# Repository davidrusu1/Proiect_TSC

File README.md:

# InkTime — Smartwatch Open Source

Un smartwatch proiectat de la zero — schematic, PCB 4 straturi, model 3D complet — bazat pe nRF52840 și un display E-Paper cu consum zero în standby.

---

## Despre proiect

InkTime este un ceas inteligent construit integral custom: fiecare componentă a fost aleasă, plasată și rutată manual, de la primul simbol în schematic până la modelul 3D pregătit pentru fabricație.

Tehnologia centrală este display-ul **E-Paper (e-ink)** — după ce afișează o imagine, o menține fără niciun consum de energie. Combinat cu modul deep sleep al nRF52840 (~1.5μA), dispozitivul poate funcționa zile întregi dintr-o baterie LiPo mică.

---

## Ce conține placa

| Subsistem | Componentă | Rol |
|---|---|---|
| Microcontroller | nRF52840 | Cortex-M4 64MHz, BT 5.0, USB nativ |
| Display | E-Paper via SPI | Afișaj fără consum în standby |
| Mișcare | BMA423 | Accelerometru 3 axe, step counter, wake-on-wrist |
| Încărcare | BQ25180 | LiPo charger programabil I2C, 5mA–1A |
| Alimentare | RT6160 | Buck-Boost 3.3V stabil indiferent de tensiunea bateriei |
| Fuel Gauge | MAX17048 | Monitorizare baterie ModelGauge, fără shunt rezistor |
| Feedback haptic | DRV2605 | Driver haptic I2C, 123 efecte ERM/LRA |
| USB | KH-TYPE-C-16P + USBLC6 | Conector USB-C cu protecție ESD ±15kV |
| Butoane | EVP-AKE31A ×3 | Butoane tactile SMD ultra-subțiri |
| RF | 2450AT18B100E | Antenă SMD 2.45GHz pentru Bluetooth |

---

## Diagrama bloc a sistemului

```
USB-C (5V)
    │
    ▼
┌─────────┐    VBUS      ┌──────────────┐
│  ESD    │─────────────▶│  BQ25180     │ LiPo Charger
│USBLC6   │              │  (I2C 0x6A)  │◀─── Baterie LiPo
└────┬────┘              └──────┬───────┘
     │ D+/D−                    │ VBAT
     │                          ▼
     │                   ┌──────────────┐
     │                   │  MAX17048    │ Fuel Gauge
     │                   │  (I2C 0x36)  │
     │                   └──────┬───────┘
     │                          │ VBAT
     │                          ▼
     │                   ┌──────────────┐
     │                   │   RT6160     │ Buck-Boost DC/DC
     │                   │  (I2C 0x62)  │─── 3V3 ──────────┐
     │                   └──────────────┘                   │
     │                                                      │
     └──────────────────────────────────────────────────────▼
                                                    ┌──────────────────┐
                  ┌── SPI ──▶ E-Paper Display       │                  │
                  │                                  │    nRF52840      │
                  ├── I2C ──▶ BMA423  (0x18)        │    Cortex-M4     │
                  │       ──▶ DRV2605 (0x5A)        │    64MHz / BT5.0 │
                  │       ──▶ BQ25180 (0x6A)        │                  │
                  │       ──▶ RT6160  (0x62)        └────────┬─────────┘
                  │       ──▶ MAX17048(0x36)                 │
                  │                                          │ GPIO
                  ├── SWD ──▶ TC2030-IDC                     │
                  │                                          ▼
                  └── USB ──▶ (intern nRF52840)      Butoane ×3 / IMU INT / HAPTIC_EN
```

---

## BOM — Bill of Materials

| Ref | Part Number | Descriere | Qty |
|---|---|---|---|
| U1 | nRF52840-QIAA-R | MCU ARM Cortex-M4, BT 5.0, USB 2.0, 1MB Flash | 1 |
| IC1 | BQ25180YBGR | LiPo charger liniar 1A I2C, 8-DSBGA | 1 |
| IC2 | DRV2605YZFR | Haptic driver ERM/LRA I2C 123 efecte, 9-BGA | 1 |
| IC3 | BMA423 | Accelerometru MEMS triaxial 12-bit, LGA-12 | 1 |
| U3 | MAX17048G+T10 | Fuel gauge ModelGauge 1-cell, SOT-23-6 | 1 |
| IC9 | RT6160AWSC | Buck-Boost DC/DC 800mA I2C, 15-WL-CSP | 1 |
| D3 | USBLC6-2SC6Y | TVS ESD ±15kV bidirecțional USB, SOT-23-6 | 1 |
| J4 | KH-TYPE-C-16P | Conector USB-C 16 pini SMD | 1 |
| J1 | 503480-2400 | Conector FPC/FFC 0.5mm pas 24 circuite | 1 |
| J2 | TC2030-IDC | Tag-Connect SWD 6 pini footprint-only | 1 |
| Q2 | DMG2305UX-7 | P-MOSFET 20V/4.2A, SOT-23 | 1 |
| Q3 | SI1308EDL-T1-GE3 | N-MOSFET 30V/1.5A, SC-70 | 1 |
| D1,D2,D5 | MBR0530 | Schottky 30V/500mA, SOD-123 | 3 |
| SW_* | EVP-AKE31A | Buton tactil SMD ultra-subțire Panasonic | 3 |
| ANT1 | 2450AT18B100E | Antenă SMD 2.45GHz Johanson | 1 |
| L7 | FTC252012SR47MBCA | Inductor 0.47μH SMD 2016 | 1 |
| L5 | 744043680 | Inductor 68μH WE-TPC SMD | 1 |
| X1 | SXT21410EC27-32.000M | Cristal SMD 32MHz | 1 |
| X2 | NX3215SA-32.768K | Cristal RTC 32.768kHz 3215 SMD | 1 |
| Cx | GJM0335C1ER33WB01D / GRM011R60J152KE01L | Condensatoare SMD 0201/0402, 1pF–22μF | ~50 |
| Rx | ERA-1AEB / CPF0201 | Rezistoare SMD 0201, 2.2Ω–10kΩ | ~15 |
| TP_* | — | Test pad SMD | 14 |

---

## Hardware în detaliu

### Cum circulă energia

Bateria LiPo (3.7–4.2V) furnizează tensiunea de intrare pentru regulatorul **RT6160**, care generează un rail stabil de 3.3V pentru întreaga placă. La conectarea USB-C, VBUS (5V) ajunge direct la **BQ25180**, care preia controlul încărcării bateriei independent de restul sistemului. nRF52840 monitorizează în permanență cele două stări: prezența USB prin semnalul CHARGER_PG și nivelul bateriei prin **MAX17048** pe magistrala I2C.

Componentele cu consum ridicat — display-ul E-Paper și driverul haptic — sunt controlate fiecare printr-un MOSFET (Q2/Q3), permițând nRF52840 să le întrerupă complet alimentarea când nu sunt necesare.

---

### Magistrala I2C — 5 periferice pe aceleași fire

| Componentă | Adresă I2C | Funcție |
|---|---|---|
| BQ25180 | 0x6A | Reglează curentul și tensiunea de încărcare |
| RT6160 | 0x62 | Ajustează tensiunea de ieșire la nevoie |
| BMA423 | 0x18 | Furnizează date accelerometru și numără pași |
| MAX17048 | 0x36 | Raportează procentul de baterie și tensiunea celulei |
| DRV2605 | 0x5A | Selectează și redă efecte tactile |

Clock pe **P0.06**, date pe **P0.07**. Rezistoare de pull-up pe ambele linii.

---

### SPI — Display E-Paper

Comunicație unidirecțională spre display — nu există linie MISO deoarece displayul nu transmite date înapoi. Frecvență maximă 4MHz. Pe lângă SCK și MOSI, display-ul necesită 3 semnale GPIO suplimentare: **DC** (Data/Command), **RST** (reset hardware) și **BUSY** (MCU-ul așteaptă când displayul procesează un refresh).

---

### SWD — Programare și debug

Conectorul **TC2030-IDC** (Tag-Connect, fără pini fizici pe PCB) expune SWDIO, SWDCLK, SWO și RESET. Nu ocupă înălțime în ansamblu — cablul de programare se atașează temporar prin spring pins pe pad-urile PCB-ului.

---

### Bluetooth și antenă

Antena **2450AT18B100E** este o antenă SMD ceramică pentru 2.4GHz, plasată spre exteriorul plăcii cu un decupaj în substrat sub ea. Decupajul elimină FR4-ul (material cu pierderi dielectrice la 2.4GHz) din zona de radiație, îmbunătățind câștigul și adaptarea de impedanță a antenei. Cristalul de 32MHz furnizează referința de frecvență pentru modulul radio.

---

### Cristalul de 32.768kHz — RTC în sleep

Al doilea oscilator alimentează timer-ul RTC al nRF52840 și rămâne activ inclusiv în deep sleep. Permite dispozitivului să mențină ora exactă și să se trezească la intervale precise fără a ține procesorul activ.

---

### BMA423 — Mai mult decât un accelerometru

BMA423 dispune de un procesor intern dedicat pentru algoritmii de step counting și wake-on-wrist, care rulează independent de nRF52840. La detectarea mișcării specifice ridicării mâinii, trimite o întrerupere pe **P1.08 (IMU_INT1)** care trezește MCU-ul din deep sleep în microsecunde. Consum în această stare: 0.9μA.

---

### Estimare consum și autonomie

| Scenariu | Curent estimat |
|---|---|
| nRF52840 TX Bluetooth activ | 6.26 mA |
| nRF52840 RX Bluetooth activ | 4.82 mA |
| Refresh display E-Paper | ~26 mA (câteva secunde) |
| BMA423 monitorizare continuă | 130 μA |
| MAX17048 fuel gauge activ | 23 μA |
| DRV2605 vibrație activă | 5 mA |
| nRF52840 deep sleep + RTC + BMA low-power | ~50–100 μA |

Consum mediu în utilizare normală (BT conectat periodic, refresh display la fiecare minut, IMU activ): **6–8 mA la 3.3V**.

Cu o baterie LiPo de **300mAh**: autonomie estimată **35–50 ore**.

---

## Alocarea pinilor nRF52840

### Display E-Paper (SPI)

| Pin MCU | Semnal | Direcție | Descriere |
|---|---|---|---|
| P0.02 / AIN0 | SCK | OUT | Clock SPI pentru display |
| P0.03 / AIN1 | MOSI | OUT | Date seriale spre display |
| P0.05 / AIN3 | EPD_CS | OUT | Chip select, activ LOW |
| P0.15 | EPD_RST | OUT | Reset hardware display, activ LOW |
| P0.16 | EPD_DC | OUT | LOW = comandă, HIGH = date |
| P0.17 | EPD_BUSY | IN | HIGH când displayul procesează |

### Periferice I2C

| Pin MCU | Semnal | Descriere |
|---|---|---|
| P0.06 | SCL | Clock comun pentru toate perifericele I2C |
| P0.07 | SDA | Date bidirecționale I2C |
| P0.08 | IMU_INT2 | Întrerupere secundară BMA423 (step counter) |
| P1.08 | IMU_INT1 | Întrerupere primară BMA423 (wake-on-wrist) |
| P0.10 / NFC2 | FUELGAUGE_ALT | Alarmă MAX17048 la baterie scăzută |
| P0.11 | CHARGER_PG | Power Good BQ25180 — HIGH când USB e valid |
| P0.12 | HAPTIC_EN | Enable DRV2605, activ HIGH |

### Butoane

| Pin MCU | Semnal | Descriere |
|---|---|---|
| P0.13 | BTN_UP | Buton sus (navigare meniu) |
| P0.14 | BTN_ENT | Buton enter / confirmare |
| P1.02 | BTN_DN | Buton jos (navigare meniu) |

### USB, SWD și ceasuri

| Pin MCU | Semnal | Interfață | Descriere |
|---|---|---|---|
| D+ | USB_DP | USB | Linie diferențială pozitivă, prin ESD |
| D− | USB_DM | USB | Linie diferențială negativă, prin ESD |
| VBUS | 5V_USB | PWR | Detecție USB prezent → BQ25180 |
| SWDIO | SWDIO | SWD | Date programare/debug |
| SWDCLK | SWDCLK | SWD | Clock programare/debug |
| SWO | SWO | SWD | Serial Wire Output (trace) |
| P0.18 / RESET | RESET | GPIO | Reset hardware MCU |
| ANT | RF | RF | Antenă Bluetooth 2.4GHz |
| XC1, XC2 | XTAL_32M | CLK | Cristal 32MHz — clock principal |
| XL1, XL2 | XTAL_32K | CLK | Cristal 32.768kHz — RTC sleep |

---

## PCB — Decizii de proiectare

### 4 straturi

| Strat | Conținut |
|---|---|
| L1 — Top | Toate componentele SMD + rutare semnale principale |
| L2 | Plan de masă GND continuu |
| L3 | Plan de alimentare 3V3 |
| L4 — Bottom | Rutare secundară + conexiuni via |

Planul de masă pe L2 direct sub stratul de semnal L1 minimizează inductanța buclei de return. Planul de 3V3 pe L3 reduce impedanța de alimentare, esențial pentru vârfurile de curent ale nRF52840 în modul TX.

### Decupaj sub antenă

FR4-ul este un material cu pierderi dielectrice la 2.4GHz. Un decupaj fizic al PCB-ului sub jumătatea neconectată a antenei 2450AT18B100E permite acesteia să radieze în aer, îmbunătățind performanța RF.

### Test pad-uri

14 test pad-uri distribuite pe semnalele: 3V3, VBAT, GND, SDA, SCL, SWDCLK, SWDIO, SWO, RESET, VREG. Permit conectarea unui multimetru sau logic analyzer după asamblare.

### Erori acceptate

- **Board Outline Clearance** — erorile generate de markerii de dimensiuni și textele de silkscreen aflate lângă marginea plăcii au fost aprobate, deoarece nu afectează fabricabilitatea PCB-ului.
- **Copper Width** pe traseele de sub componentele BGA — lățimea a fost redusă local pentru a permite rutarea prin pitch-ul mic al pad-urilor BGA, apoi adusă înapoi la 0.3mm după ieșirea din zona BGA.

---

## Ansamblu 3D

Modelat complet în Autodesk Fusion 360. Stratificarea de jos în sus:

```
┌─────────────────────────┐  ← Cadru superior + geam display
│     Display E-Paper     │  ← Panou e-ink + cablu FPC
│         PCB             │  ← Placa cu toate componentele
│      Baterie LiPo       │  ← Celulă lipită direct pe test pad-uri
└─────────────────────────┘  ← Carcasă inferioară
```

Butoanele (×3) sunt accesibile prin locașurile laterale ale carcasei. Conectorul USB-C iese prin fanta frontală. Shaker-ul haptic este montat în spațiul rămas lângă baterie.

---

## Galerie

---

## Structura repository-ului

```
InkTime/
│
├── Hardware/
│   ├── PCB.brd                  # Fișier board Fusion Electronics
│   ├── Schematic_Final.sch      # Schematic complet
│   └── Schematic_Final.pdf      # Export PDF schematic
│
├── Manufacturing/
│   ├── gerbers.zip              # Fișiere Gerber pentru fabricație
│   ├── InkTime.bom              # Bill of Materials
│   └── PnP_InkTime_front.cpl   # Pick & Place față
│
├── Mechanical/
│   ├── Exploded_Watch3D.zip    # Exported STEP ansamblu exploded view
│   └── Assembled Watch.f3z           # Proiect Autodesk Fusion 360
│
├── Images/                      # Randări și capturi PCB
│
├── LICENSE
└── README.md
```

---

MIT License — Copyright 2026 Rusu David Gabriel

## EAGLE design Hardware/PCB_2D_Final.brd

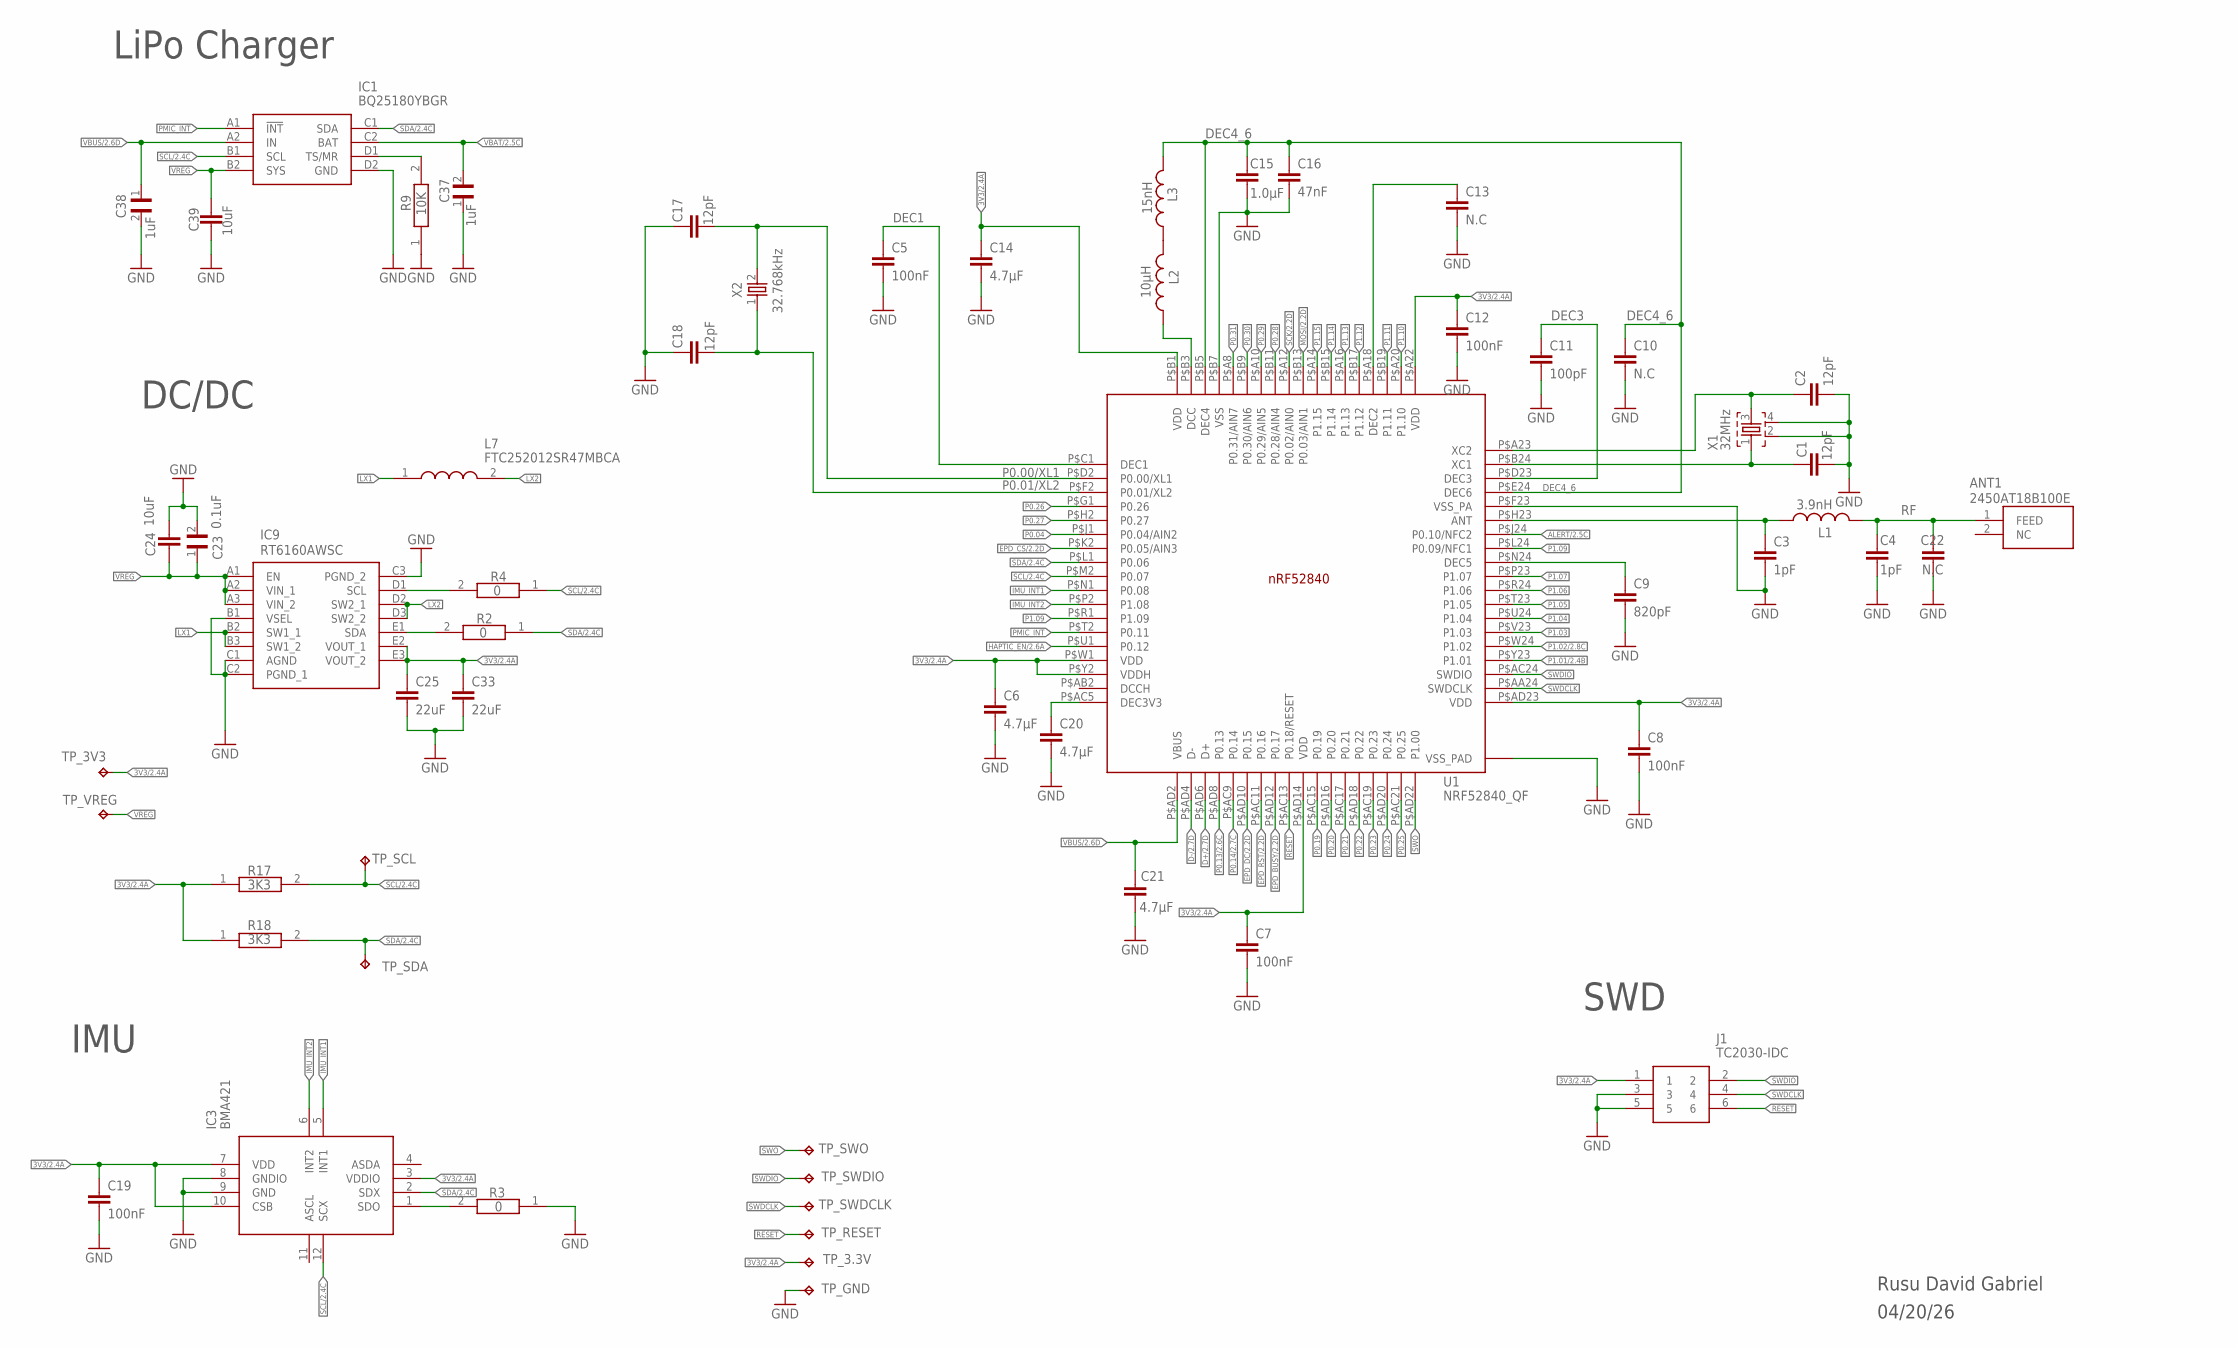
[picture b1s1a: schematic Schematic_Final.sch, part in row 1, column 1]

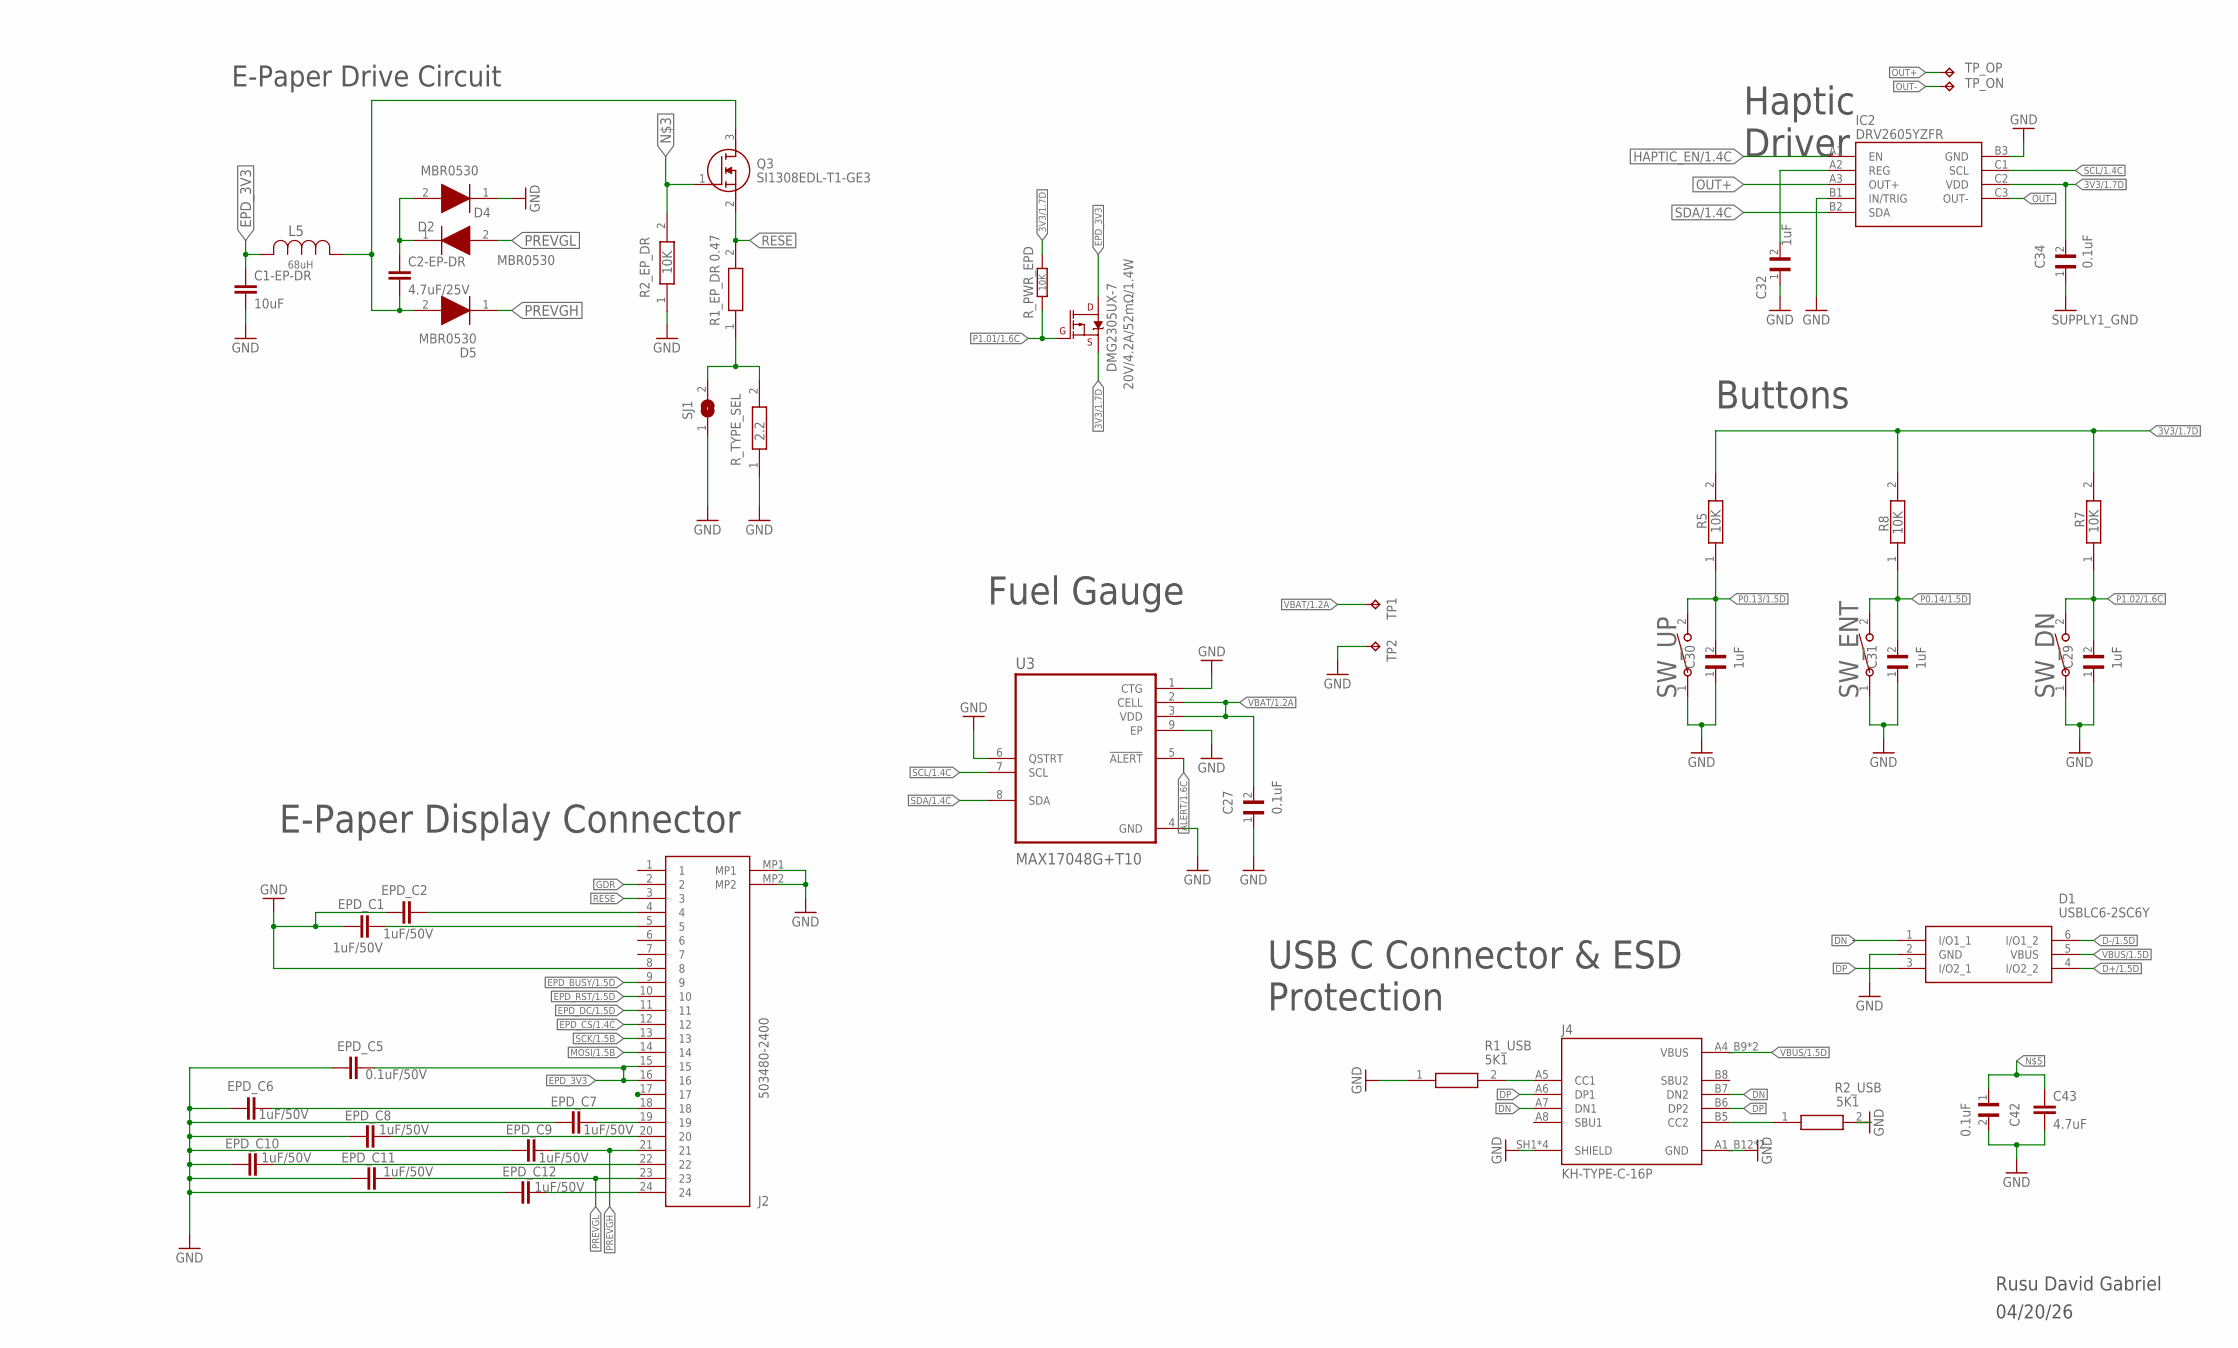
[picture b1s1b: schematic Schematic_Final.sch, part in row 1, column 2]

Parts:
ANT1: 2450AT18B100E; 2450AT18B100E_ANTC3216X140N
C1, C2, C17, C18: 12pF; NORDIC_NRF_3_RESC0201_L
C1-EP-DR, C24, C39: 10uF; NORDIC_NRF_3_RESC0402_L
C2-EP-DR: 4.7uF/25V; NORDIC_NRF_3_RESC0402_L
C3, C4: 1pF; NORDIC_NRF_3_RESC0201_L
C5, C7, C8, C12, C19: 100nF; NORDIC_NRF_3_RESC0201_L
C6, C14, C20, C21: 4.7μF; NORDIC_NRF_3_RESC0402_L
C9: 820pF; NORDIC_NRF_3_RESC0201_L
C10, C13, C22: N.C; NORDIC_NRF_3_RESC0201_L
C11: 100pF; NORDIC_NRF_3_RESC0201_L
C15: 1.0μF; NORDIC_NRF_3_RESC0402_L
C16: 47nF; NORDIC_NRF_3_RESC0201_L
C23, C27, C34, C42: 0.1uF; GRM011R60J152KE01L_2_CAPC0201X13N
C25, C33: 22uF; NORDIC_NRF_3_RESC0402_L
C29, C30, C31, C32, C37, C38: 1uF; GRM011R60J152KE01L_2_CAPC0201X13N
C43: 4.7uF; NORDIC_NRF_3_RESC0402_L
D1: USBLC6-2SC6Y; ESP32_C6_LIBRARY_3_SOT95P280X145-6N
D2, D4, D5: MBR0530; ESP32_C6_LIBRARY_5_SOD3716X135N
DMG2305UX-7: 20V/4.2A/52mΩ/1.4W; ESP32_C6_LIBRARY_4_ESP32_C6_LIBRARY_4_ESP32_C6_LIBRARY_4_ES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
EPD_C1, EPD_C2, EPD_C6, EPD_C7, EPD_C8, EPD_C9, EPD_C10, EPD_C11, EPD_C12: 1uF/50V; NORDIC_NRF_3_RESC0402_L
EPD_C5: 0.1uF/50V; NORDIC_NRF_3_RESC0201_L
IC1: BQ25180YBGR; BQ25180YBGR_BGA8C40P2X4_100X155X50
IC2: DRV2605YZFR; DRV2605YZFR_BGA9C50P3X3_144X144X62
IC3: BMA421; BMA423_BMA423
IC9: RT6160AWSC; RT6160AWSC_BGA15C40P3X5_140X230X60
J1: TC2030-IDC; TC2030-IDC_TC2030IDC
J2: 503480-2400; 503480-2400_5034802400
J4: KH-TYPE-C-16P; KH-TYPE-C-16P_KINGHELM_KH-TYPE-C-16P
L1: 3.9nH; NORDIC_NRF_2_RESC0402_L
L2: 10μH; NORDIC_NRF_2_RESC0402_L
L3: 15nH; NORDIC_NRF_2_RESC0402_L
L5: 68uH; ESP32_C6_LIBRARY_2_IND_4828-WE-TPC_WRE
L7: FTC252012SR47MBCA; MLP2016SR47MT0S1_INDC2016X100N
Q3: SI1308EDL-T1-GE3; ESP32_C6_LIBRARY_6_SOT65P210X110-3N
R1_EP_DR: 0.47; CPF0201D7K68C1_0201
R1_USB, R2_USB: 5K1; CPF0201D7K68C1_0201
R2, R3, R4: 0; CPF0201D7K68C1_0201
R2_EP_DR, R5, R7, R8, R9: 10K; CPF0201D7K68C1_0201
R17, R18: 3K3; CPF0201D7K68C1_0201
R_PWR_EPD: 10K; RESC1005X40
R_TYPE_SEL: 2.2; CPF0201D7K68C1_0201
SJ1: ESP32_C6_LIBRARY_7_JUMPER_SJ
SW_DN: 2025-10-22_07-23-44_LIBRARY_EVP-AKE31ASW_EVP-AKE3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; 2025-10-22_07-23-44_LIBRARY_SW_EVP-AKE31A_PAN
SW_ENT: 2025-10-22_07-23-44_LIBRARY_EVP-AKE31ASW_EVP-AKE3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; 2025-10-22_07-23-44_LIBRARY_SW_EVP-AKE31A_PAN
SW_UP: 2025-10-22_07-23-44_LIBRARY_EVP-AKE31ASW_EVP-AKE3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; 2025-10-22_07-23-44_LIBRARY_SW_EVP-AKE31A_PAN
TP1, TP2: HECTOR_WATCH_1_TPTP20R; HECTOR_WATCH_1_TP20R
TP_3.3V, TP_3V3: HECTOR_WATCH_1_TPTP20R; HECTOR_WATCH_1_TP20R
TP_GND: HECTOR_WATCH_1_TPTP20R; HECTOR_WATCH_1_TP20R
TP_ON: HECTOR_WATCH_1_TPTP20R; HECTOR_WATCH_1_TP20R
TP_OP: TP_OP; HECTOR_WATCH_1_TP20R
TP_RESET: HECTOR_WATCH_1_TPTP20R; HECTOR_WATCH_1_TP20R
TP_SCL: HECTOR_WATCH_1_TPTP20R; HECTOR_WATCH_1_TP20R
TP_SDA: HECTOR_WATCH_1_TPTP20R; HECTOR_WATCH_1_TP20R
TP_SWDCLK: HECTOR_WATCH_1_TPTP20R; HECTOR_WATCH_1_TP20R
TP_SWDIO: HECTOR_WATCH_1_TPTP20R; HECTOR_WATCH_1_TP20R
TP_SWO: HECTOR_WATCH_1_TPTP20R; HECTOR_WATCH_1_TP20R
TP_VREG: HECTOR_WATCH_1_TPTP20R; HECTOR_WATCH_1_TP20R
U1: NRF52840_QF; NORDIC_NRF_4_AQFN50P700X700X85_HS-74N
U3: MAX17048G+T10; ESP32_C6_LIBRARY_SON50P200X200X80-9N
X1: 32MHz; NORDIC_NRF_BT-XTAL_2016_N
X2: 32.768kHz; NORDIC_NRF_1_XTAL_3215_N

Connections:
3V3/1.7D: C34.2, DMG2305UX-7.2 (S), IC2.C2 (VDD), R5.2, R7.2, R8.2, R_PWR_EPD.2
3V3/2.4A: C6.1, C7.1, C8.1, C12.1, C14.1, C19.1, C25.1, C33.1, IC3.3 (VDDIO), IC3.7 (VDD), IC3.10 (CSB), IC9.E2 (VOUT_1), IC9.E3 (VOUT_2), J1.1, R17.1, R18.1, TP_3.3V.TP, TP_3V3.TP, U1.P$A22 (VDD), U1.P$AD14 (VDD), U1.P$AD23 (VDD), U1.P$B1 (VDD), U1.P$W1 (VDD), U1.P$Y2 (VDDH)
ALERT/1.6C: U3.5 (!ALERT)
ALERT/2.5C: U1.P$J24 (P0.10/NFC2)
D+/1.5D: D1.4 (I/O2_2)
D+/2.7D: U1.P$AD6 (D+)
D-/1.5D: D1.6 (I/O1_2)
D-/2.7D: U1.P$AD4 (D-)
DEC1: C5.1, U1.P$C1 (DEC1)
DEC3: C11.1, U1.P$D23 (DEC3)
DEC4_6: C10.1, C15.1, C16.1, L3.2, U1.P$B5 (DEC4), U1.P$E24 (DEC6)
DN: D1.1 (I/O1_1), J4.A7 (DN1), J4.B7 (DN2)
DP: D1.3 (I/O2_1), J4.A6 (DP1), J4.B6 (DP2)
EPD_3V3: C1-EP-DR.1, DMG2305UX-7.3 (D), EPD_C5.2, J2.15, J2.16, L5.2
EPD_BUSY/1.5D: J2.9
EPD_BUSY/2.2D: U1.P$AD12 (P0.17)
EPD_CS/1.4C: J2.12
EPD_CS/2.2D: U1.P$K2 (P0.05/AIN3)
EPD_DC/1.5D: J2.11
EPD_DC/2.2D: U1.P$AD10 (P0.15)
EPD_RST/1.5D: J2.10
EPD_RST/2.2D: U1.P$AC11 (P0.16)
GDR: J2.2
GND: C1.2, C1-EP-DR.2, C2.2, C3.2, C4.2, C5.2, C6.2, C7.2, C8.2, C9.2, C10.2, C11.2, C12.2, C13.2, C14.2, C15.2, C16.2, C17.1, C18.1, C19.2, C20.2, C21.2, C22.2, C23.2, C24.1, C25.2, C27.1, C29.1, C30.1, C31.1, C32.1, C33.2, C34.1, C37.1, C38.2, C39.2, C42.2, C43.2, D1.2 (GND), D4.1 (K), EPD_C1.1, EPD_C2.1, EPD_C5.1, EPD_C6.1, EPD_C7.1, EPD_C8.1, EPD_C9.1, EPD_C10.1, EPD_C11.1, EPD_C12.1, IC1.D2 (GND), IC2.B1 (IN/TRIG), IC2.B3 (GND), IC3.8 (GNDIO), IC3.9 (GND), IC9.B1 (VSEL), IC9.C1 (AGND), IC9.C2 (PGND_1), IC9.C3 (PGND_2), J1.3, J1.5, J2.8, J2.17, J2.MP1, J2.MP2, J4.A1_B12 (GND), J4.A12_B1 (GND), J4.SH1 (SHIELD), J4.SH2 (SHIELD), J4.SH3 (SHIELD), J4.SH4 (SHIELD), R1_USB.1, R2_EP_DR.1, R2_USB.2, R3.1, R9.1, R_TYPE_SEL.1, SJ1.1, SW_DN.1, SW_ENT.1, SW_UP.1, TP2.TP, TP_GND.TP, U1.P$74 (VSS_PAD), U1.P$75 (VSS_PAD), U1.P$76 (VSS_PAD), U1.P$77 (VSS_PAD), U1.P$78 (VSS_PAD), U1.P$79 (VSS_PAD), U1.P$80 (VSS_PAD), U1.P$81 (VSS_PAD), U1.P$82 (VSS_PAD), U1.P$83 (VSS_PAD), U1.P$84 (VSS_PAD), U1.P$85 (VSS_PAD), U1.P$86 (VSS_PAD), U1.P$87 (VSS_PAD), U1.P$88 (VSS_PAD), U1.P$89 (VSS_PAD), U1.P$90 (VSS_PAD), U1.P$B7 (VSS), U1.P$F23 (VSS_PA), U3.1 (CTG), U3.4 (GND), U3.6 (QSTRT), U3.9 (EP), X1.2, X1.4
HAPTIC_EN/1.4C: IC2.A1 (EN)
HAPTIC_EN/2.6A: U1.P$U1 (P0.12)
IMU_INT1: IC3.5 (INT1), U1.P$N1 (P0.08)
IMU_INT2: IC3.6 (INT2), U1.P$P2 (P1.08)
LX1: IC9.B2 (SW1_1), IC9.B3 (SW1_2), L7.1
LX2: IC9.D2 (SW2_1), IC9.D3 (SW2_2), L7.2
MOSI/1.5B: J2.14
MOSI/2.2D: U1.P$B13 (P0.03/AIN1)
unnamed: IC9.D1 (SCL), R4.2
unnamed: IC3.1 (SDO), R3.2
unnamed: IC9.E1 (SDA), Q3.1 (G), R2.2, R2_EP_DR.2
unnamed: C2-EP-DR.2, D5.2 (A), L5.1, Q3.3 (D)
unnamed: C42.1, C43.1, IC1.D1 (TS/MR), R9.2
unnamed: C2-EP-DR.1, D2.1 (K), D4.2 (A)
unnamed: R1_EP_DR.1, R_TYPE_SEL.2, SJ1.2
unnamed: C32.2, IC2.A2 (REG)
unnamed: J4.A5 (CC1), R1_USB.2
unnamed: EPD_C2.2, J2.4
unnamed: EPD_C1.2, J2.5
unnamed: J4.B5 (CC2), R2_USB.1
unnamed: C20.1, U1.P$AC5 (DEC3V3)
unnamed: EPD_C6.2, J2.18
unnamed: EPD_C7.2, J2.19
unnamed: EPD_C8.2, J2.20
unnamed: EPD_C10.2, J2.22
unnamed: EPD_C12.2, J2.24
unnamed: C9.1, U1.P$N24 (DEC5)
unnamed: C3.1, L1.1, U1.P$H23 (ANT)
unnamed: C2.1, U1.P$A23 (XC2), X1.3
unnamed: C1.1, U1.P$B24 (XC1), X1.1
unnamed: C13.1, U1.P$A18 (DEC2)
unnamed: L2.1, U1.P$B3 (DCC)
unnamed: L2.2, L3.1
OUT+: IC2.A3 (OUT+), TP_OP.TP
OUT-: IC2.C3 (OUT-), TP_ON.TP
P0.00/XL1: C17.2, U1.P$D2 (P0.00/XL1), X2.2
P0.01/XL2: C18.2, U1.P$F2 (P0.01/XL2), X2.1
P0.04: U1.P$J1 (P0.04/AIN2)
P0.13/1.5D: C30.2, R5.1, SW_UP.2
P0.13/2.6C: U1.P$AD8 (P0.13)
P0.14/1.5D: C31.2, R8.1, SW_ENT.2
P0.14/2.7C: U1.P$AC9 (P0.14)
P0.19: U1.P$AC15 (P0.19)
P0.20: U1.P$AD16 (P0.20)
P0.21: U1.P$AC17 (P0.21)
P0.22: U1.P$AD18 (P0.22)
P0.23: U1.P$AC19 (P0.23)
P0.24: U1.P$AD20 (P0.24)
P0.25: U1.P$AC21 (P0.25)
P0.26: U1.P$G1 (P0.26)
P0.27: U1.P$H2 (P0.27)
P0.28: U1.P$B11 (P0.28/AIN4)
P0.29: U1.P$A10 (P0.29/AIN5)
P0.30: U1.P$B9 (P0.30/AIN6)
P0.31: U1.P$A8 (P0.31/AIN7)
P1.01/1.6C: DMG2305UX-7.1 (G), R_PWR_EPD.1
P1.01/2.4B: U1.P$Y23 (P1.01)
P1.02/1.6C: C29.2, R7.1, SW_DN.2
P1.02/2.8C: U1.P$W24 (P1.02)
P1.03: U1.P$V23 (P1.03)
P1.04: U1.P$U24 (P1.04)
P1.05: U1.P$T23 (P1.05)
P1.06: U1.P$R24 (P1.06)
P1.07: U1.P$P23 (P1.07)
P1.09: U1.P$L24 (P0.09/NFC1), U1.P$R1 (P1.09)
P1.10: U1.P$A20 (P1.10)
P1.11: U1.P$B19 (P1.11)
P1.12: U1.P$B17 (P1.12)
P1.13: U1.P$A16 (P1.13)
P1.14: U1.P$B15 (P1.14)
P1.15: U1.P$A14 (P1.15)
PMIC_INT: IC1.A1 (!INT), U1.P$T2 (P0.11)
PREVGH: D5.1 (K), EPD_C9.2, J2.21
PREVGL: D2.2 (A), EPD_C11.2, J2.23
RESE: J2.3, Q3.2 (S), R1_EP_DR.2
RESET: J1.6, TP_RESET.TP, U1.P$AC13 (P0.18/RESET)
RF: ANT1.1 (FEED), C4.1, C22.1, L1.2
SCK/1.5B: J2.13
SCK/2.2D: U1.P$A12 (P0.02/AIN0)
SCL/1.4C: IC2.C1 (SCL), U3.7 (SCL)
SCL/2.4C: IC1.B1 (SCL), IC3.12 (SCX), R4.1, R17.2, TP_SCL.TP, U1.P$M2 (P0.07)
SDA/1.4C: IC2.B2 (SDA), U3.8 (SDA)
SDA/2.4C: IC1.C1 (SDA), IC3.2 (SDX), R2.1, R18.2, TP_SDA.TP, U1.P$L1 (P0.06)
SWDCLK: J1.4, TP_SWDCLK.TP, U1.P$AA24 (SWDCLK)
SWDIO: J1.2, TP_SWDIO.TP, U1.P$AC24 (SWDIO)
SWO: TP_SWO.TP, U1.P$AD22 (P1.00)
VBAT/1.2A: C27.2, TP1.TP, U3.2 (CELL), U3.3 (VDD)
VBAT/2.5C: C37.2, IC1.C2 (BAT)
VBUS/1.5D: D1.5 (VBUS), J4.A4_B9 (VBUS), J4.A9_B4 (VBUS)
VBUS/2.6D: C21.1, C38.1, IC1.A2 (IN), U1.P$AD2 (VBUS)
VREG: C23.1, C24.2, C39.1, IC1.B2 (SYS), IC9.A1 (EN), IC9.A2 (VIN_1), IC9.A3 (VIN_2), TP_VREG.TP

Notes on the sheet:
LiPo Charger
DC/DC
IMU
SWD
E-Paper Drive Circuit
Fuel Gauge
E-Paper Display Connector
Buttons
Haptic Driver
USB C Connector & ESD Protection
Rusu David Gabriel
04/20/26

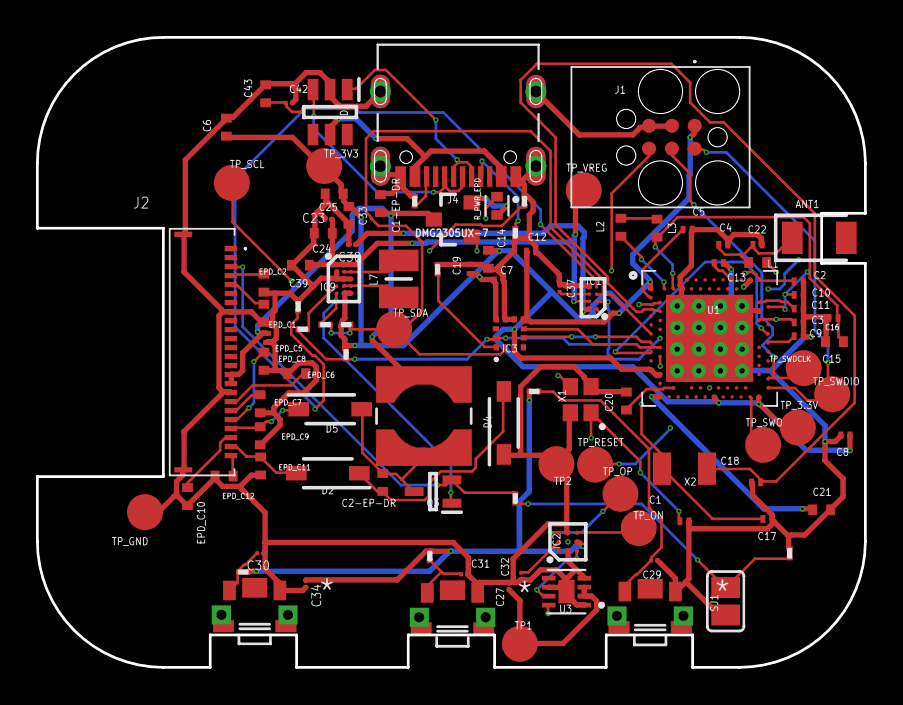
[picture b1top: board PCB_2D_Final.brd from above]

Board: 4 copper layers, 46.0 x 35.0 mm, 105 parts (0 on the bottom side), 65 nets.

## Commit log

2026-04-10 Add nimic.txt to Mechanical directory
2026-04-10 Add nimic.txt with initial content
2026-04-20 Revise README for InkTime smartwatch project
    Updated project description and details for InkTime smartwatch, including specifications, components, and functionality.

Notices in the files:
parts and their libraries:
COPYRIGHT: Copyright (C) 2024 Ultra Librarian. All rights reserved.
COPYRIGHT: Copyright (C) 2025 Ultra Librarian. All rights reserved.
